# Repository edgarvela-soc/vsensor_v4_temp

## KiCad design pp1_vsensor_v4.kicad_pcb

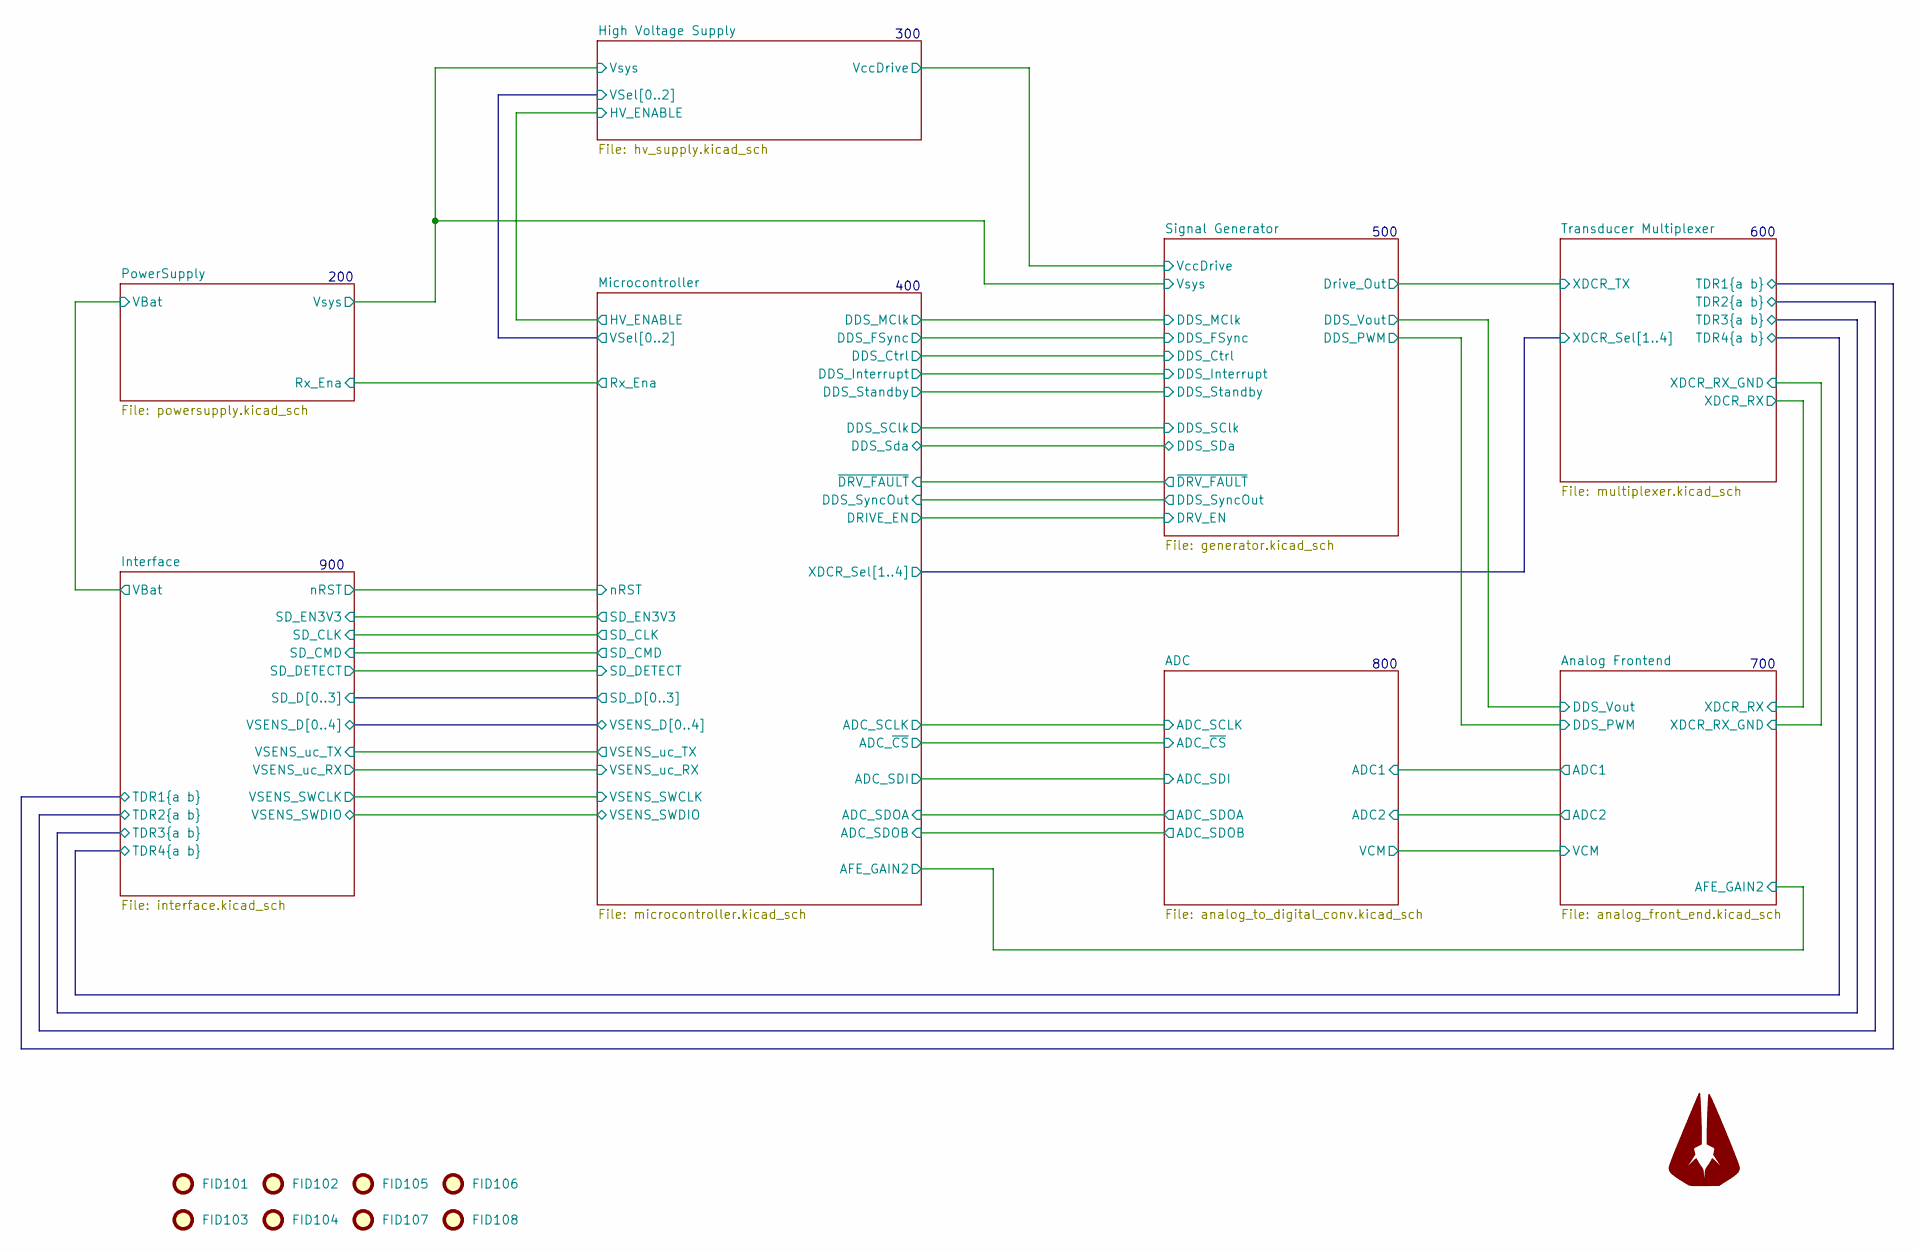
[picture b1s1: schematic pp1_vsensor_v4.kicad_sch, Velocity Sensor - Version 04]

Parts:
FID101, FID102, FID103, FID104, FID105, FID106, FID107, FID108: Fiducial; Fiducial_0.5mm_Mask1mm
Logo101: LOGO_AGU; AGU_15mm

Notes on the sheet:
700
400
800
500
300
600
900
200

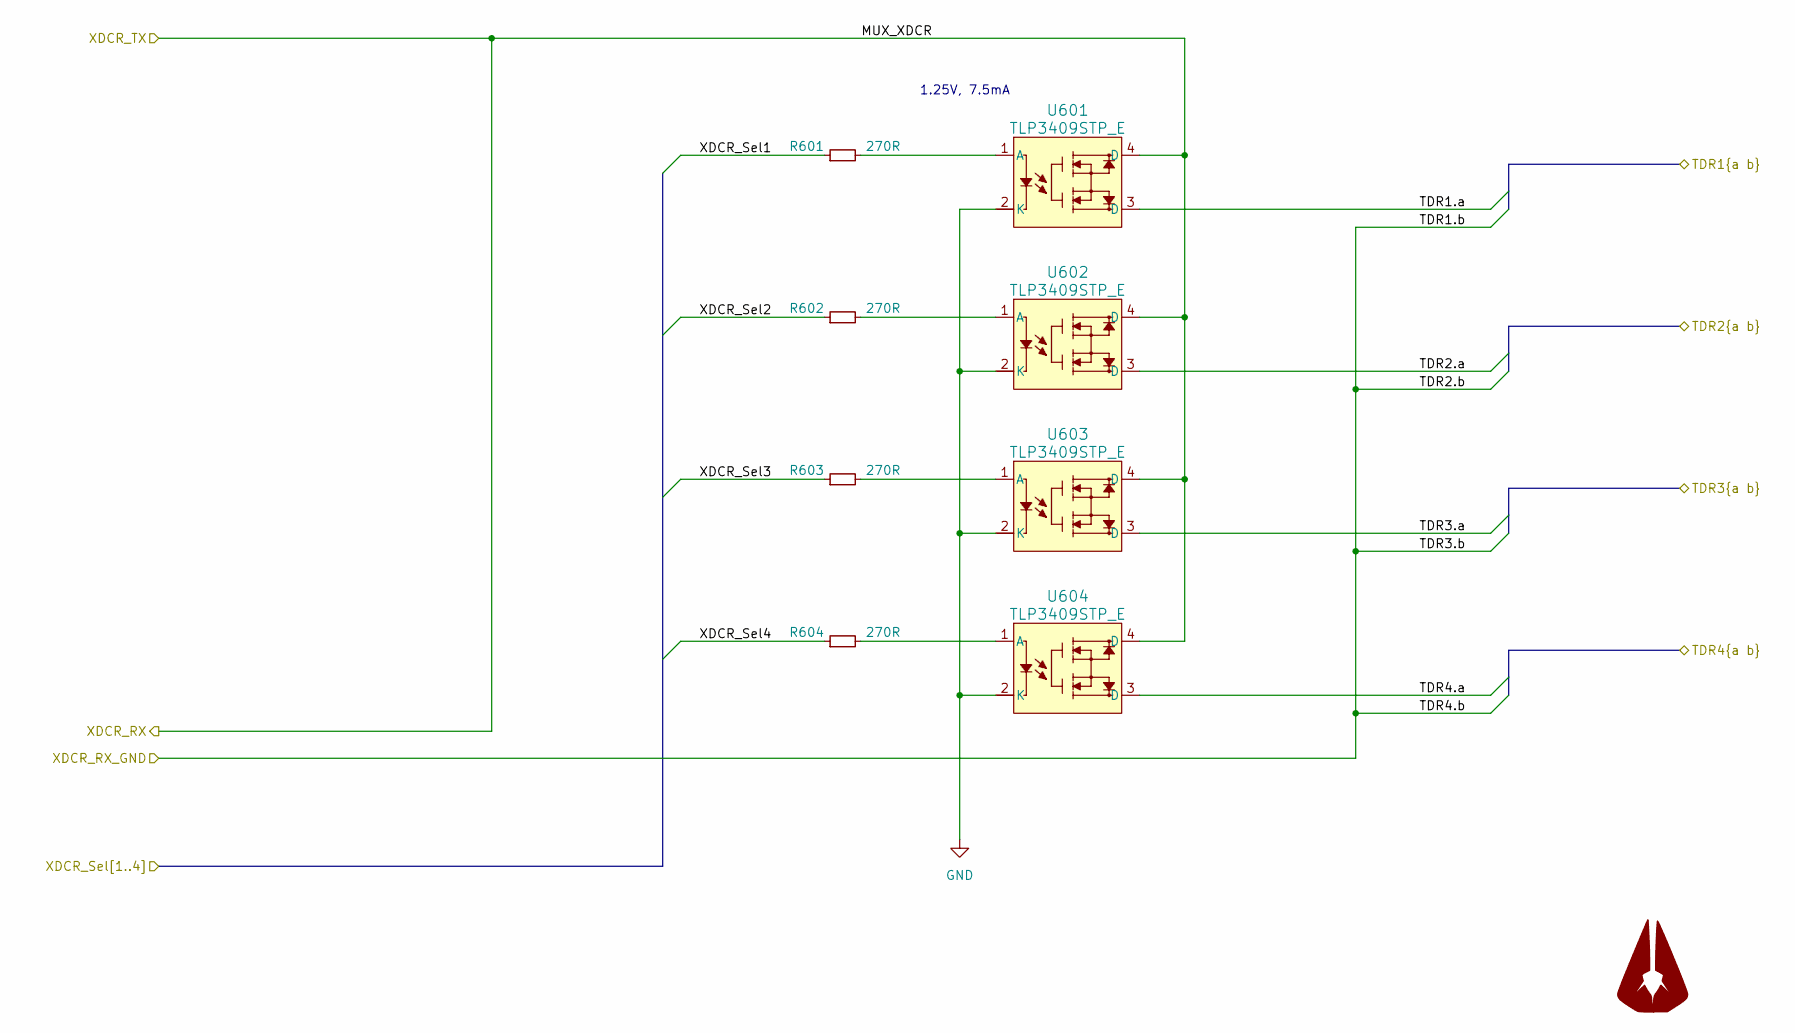
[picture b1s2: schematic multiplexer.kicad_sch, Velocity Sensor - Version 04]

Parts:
Logo601: LOGO_AGU; AGU_15mm
R601, R602, R603, R604: 270R; R_0402_1005Metric; MPN RMCF0402FT270R; Digikey_PN RMCF0402FT270RCT-ND
U601, U602, U603, U604: TLP3409STP_E; MPN TLP3409S(TP,E; Mouser_PN 757-TLP3409STPE

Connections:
/Interface/TDR1.a: U601.3 (D); also elsewhere on the board
/Interface/TDR2.a: U602.3 (D); also elsewhere on the board
/Interface/TDR3.a: U603.3 (D); also elsewhere on the board
/Interface/TDR4.a: U604.3 (D); also elsewhere on the board
/Microcontroller/XDCR_Sel1: R601.1; also elsewhere on the board
/Microcontroller/XDCR_Sel2: R602.1; also elsewhere on the board
/Microcontroller/XDCR_Sel3: R603.1; also elsewhere on the board
/Microcontroller/XDCR_Sel4: R604.1; also elsewhere on the board
/Transducer Multiplexer/MUX_XDCR: U601.4 (D), U602.4 (D), U603.4 (D), U604.4 (D); also elsewhere on the board
unnamed: R601.2, U601.1 (A)
unnamed: R602.2, U602.1 (A)
unnamed: R603.2, U603.1 (A)
unnamed: R604.2, U604.1 (A)

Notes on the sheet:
1.25V, 7.5mA

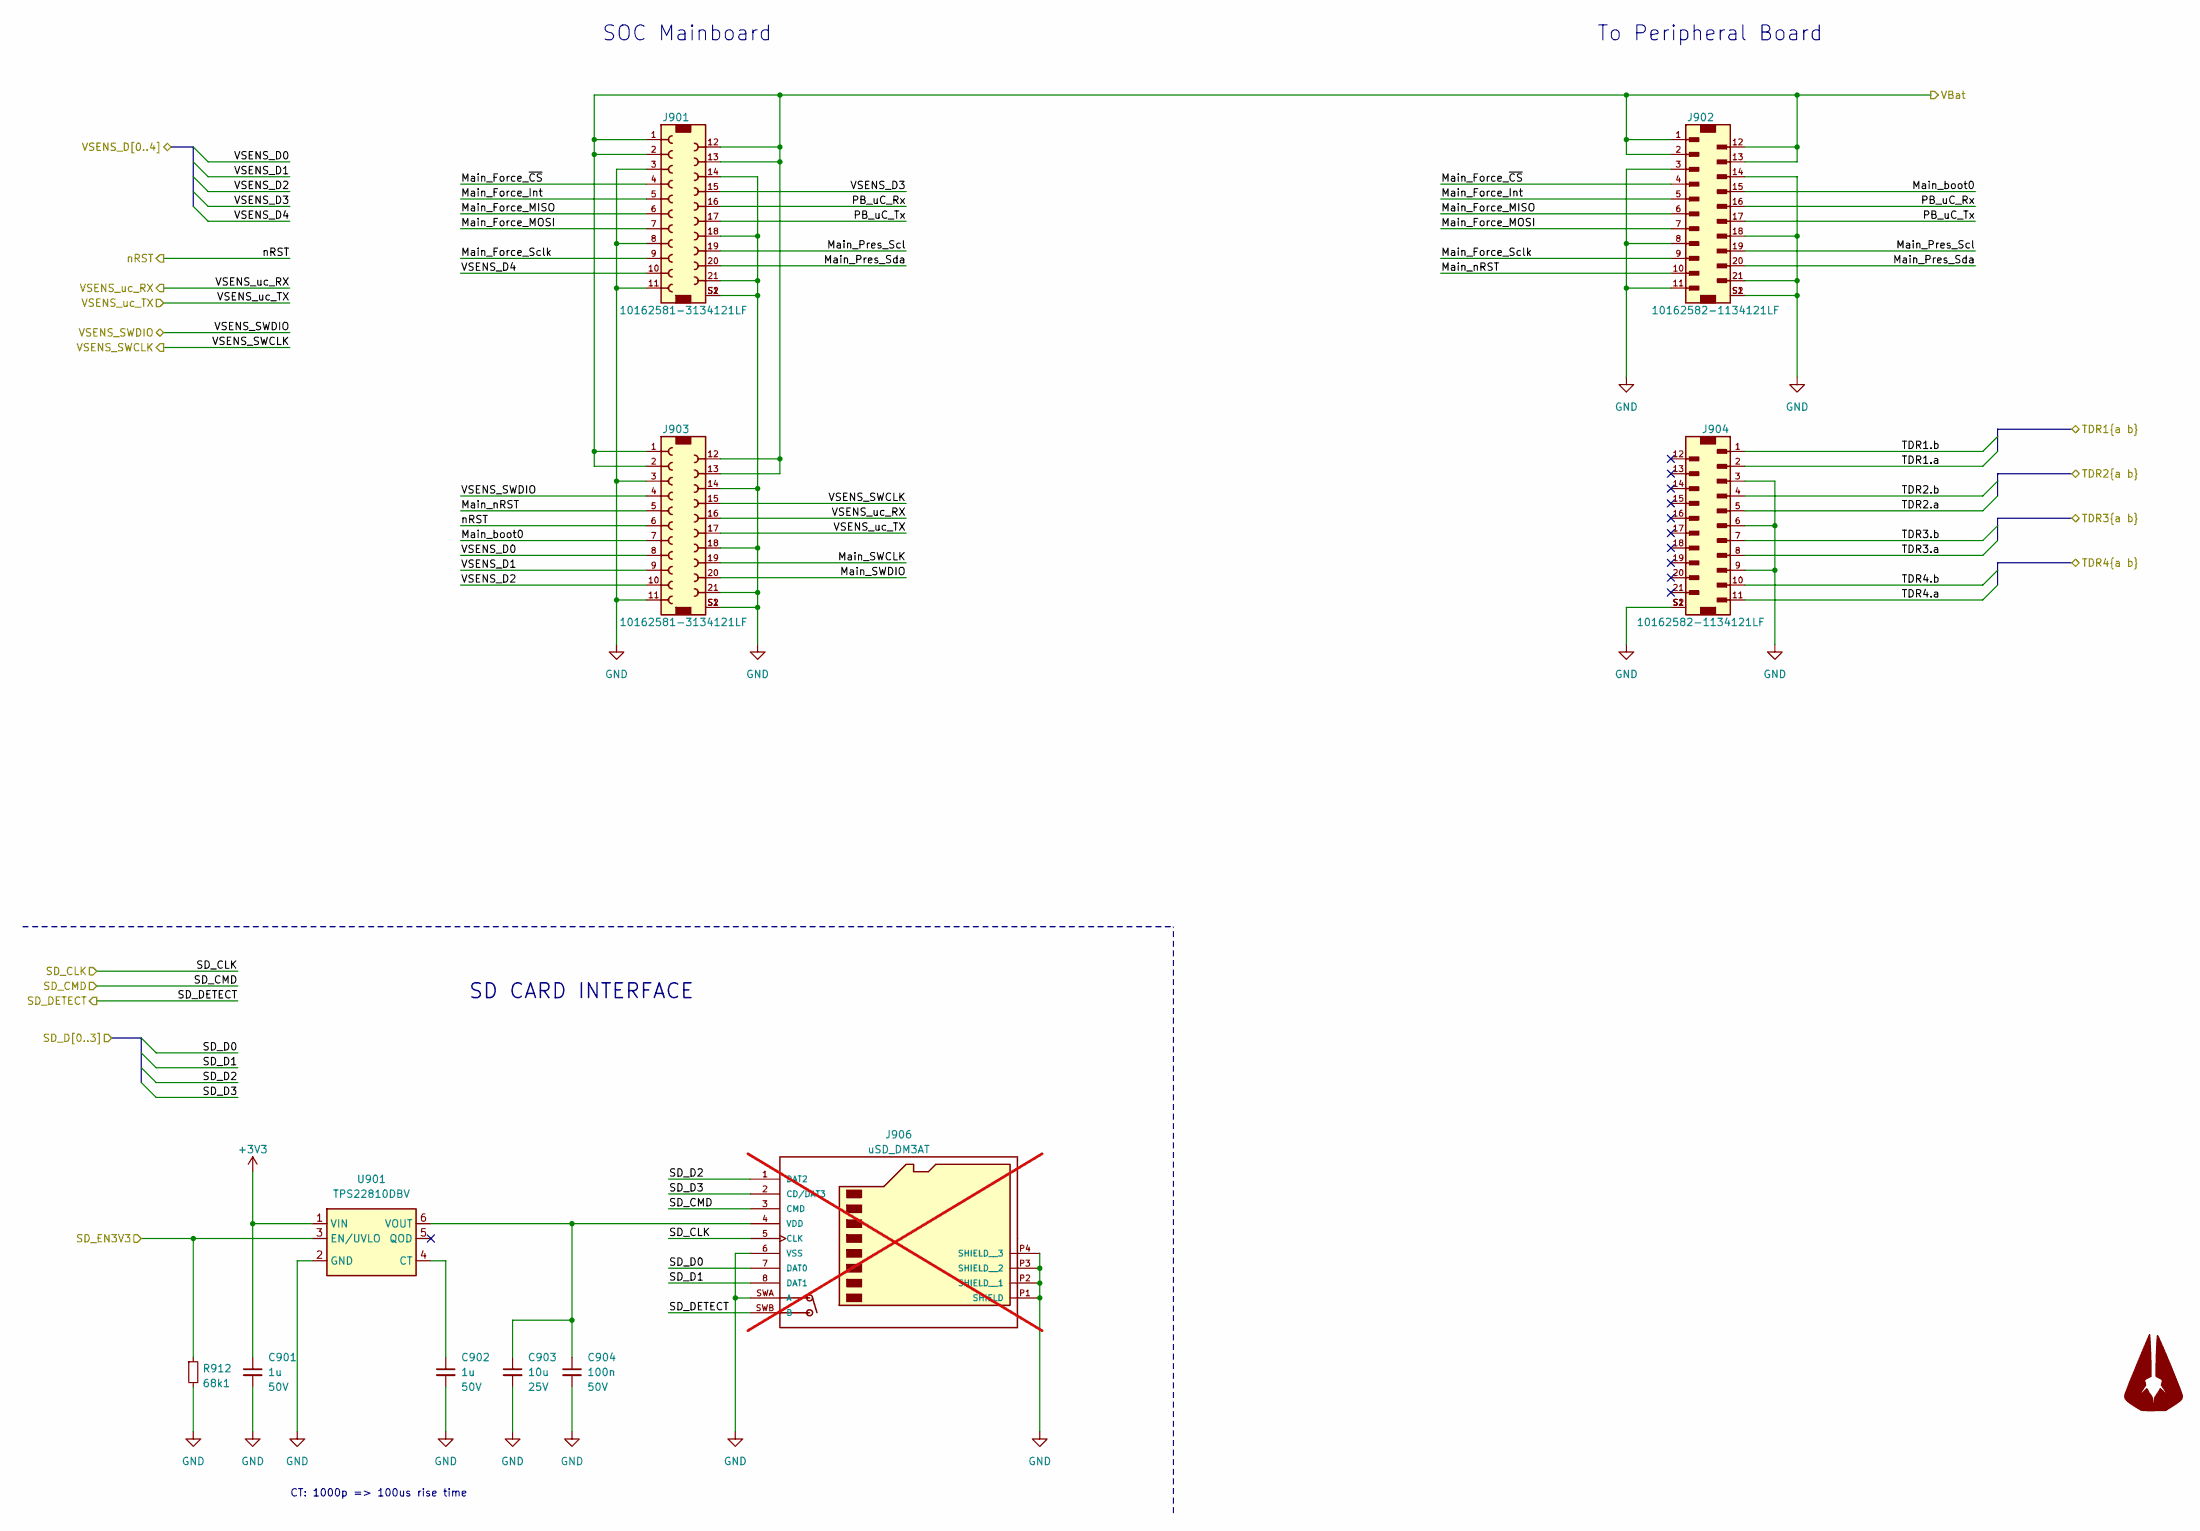
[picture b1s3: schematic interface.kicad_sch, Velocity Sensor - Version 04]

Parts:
C901, C902: 1u; C_0402_1005Metric; Voltage 50V; MPN UMK105CBJ105MV-F; Digikey_PN 587-6278-1-ND
C903: 10u; C_0603_1608Metric; Voltage 25V; MPN GRM188R61E106MA73D; Mouser_PN 81-GRM188R61E106MA3D
C904: 100n; C_0402_1005Metric; Voltage 50V; MPN CC0402KRX7R9BB104; Digikey_PN 311-3566-1-ND
J901, J903: 10162581-3134121LF; AMPHENOL_10162581-3134121LF; MPN 10162581-3134121LF; Digikey_PN 609-10162581-3134121LFCT-ND
J902, J904: 10162582-1134121LF; AMPHENOL_10162582-1134121LF; MPN 10162582-1134121LF; Digikey_PN 609-10162582-1134121LFCT-ND
J906: uSD_DM3AT; HRS_DM3AT-SF-PEJM5; PARTREV 20200913; Digikey_PN HR1964CT-ND; not fitted
Logo901: LOGO_AGU; AGU_15mm
R912: 68k1; R_0402_1005Metric; MPN RC0402FR-0768K1L; Digikey_PN YAG3213CT-ND
U901: TPS22810DBV; SOT95P280X145-6N; MPN TPS22810TDBVRQ1; Digikey_PN 296-50496-1-ND

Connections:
+3V3: C901.1, U901.1 (VIN); also elsewhere on the board
/Interface/Main_Force_Int: J901.5, J902.5
/Interface/Main_Force_MISO: J901.6, J902.6
/Interface/Main_Force_MOSI: J901.7, J902.7
/Interface/Main_Force_Sclk: J901.9, J902.9
/Interface/Main_Force_~CS: J901.4, J902.4
/Interface/Main_Pres_Scl: J901.19, J902.19
/Interface/Main_Pres_Sda: J901.20, J902.20
/Interface/Main_SWCLK: J903.19
/Interface/Main_SWDIO: J903.20
/Interface/Main_boot0: J902.15, J903.7
/Interface/Main_nRST: J902.10, J903.5
/Interface/PB_uC_Rx: J901.16, J902.16
/Interface/PB_uC_Tx: J901.17, J902.17
/Interface/SD_CLK: J906.5 (CLK); also elsewhere on the board
/Interface/SD_CMD: J906.3 (CMD); also elsewhere on the board
/Interface/SD_D0: J906.7 (DAT0); also elsewhere on the board
/Interface/SD_D1: J906.8 (DAT1); also elsewhere on the board
/Interface/SD_D2: J906.1 (DAT2); also elsewhere on the board
/Interface/SD_D3: J906.2 (CD/DAT3); also elsewhere on the board
/Interface/SD_DETECT: J906.SWB (B); also elsewhere on the board
/Interface/TDR1.a: J904.2; also elsewhere on the board
/Interface/TDR2.a: J904.5; also elsewhere on the board
/Interface/TDR3.a: J904.8; also elsewhere on the board
/Interface/TDR4.a: J904.11; also elsewhere on the board
/Interface/VBat: J901.1, J901.2, J901.12, J901.13, J902.1, J902.2, J902.12, J902.13, J903.1, J903.2, J903.12, J903.13; also elsewhere on the board
/Interface/VSENS_D0: J903.8; also elsewhere on the board
/Interface/VSENS_D1: J903.9; also elsewhere on the board
/Interface/VSENS_D2: J903.10; also elsewhere on the board
/Interface/VSENS_D3: J901.15; also elsewhere on the board
/Interface/VSENS_D4: J901.10; also elsewhere on the board
/Interface/VSENS_SWCLK: J903.15; also elsewhere on the board
/Interface/VSENS_SWDIO: J903.4; also elsewhere on the board
/Interface/VSENS_uc_RX: J903.16; also elsewhere on the board
/Interface/VSENS_uc_TX: J903.17; also elsewhere on the board
/Interface/nRST: J903.6; also elsewhere on the board
/Microcontroller/SD_EN3V3: R912.1, U901.3 (EN/UVLO); also elsewhere on the board
unnamed: C903.1, C904.1, J906.4 (VDD), U901.6 (VOUT)
unnamed: C902.1, U901.4 (CT)

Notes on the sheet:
To Peripheral Board
SOC Mainboard
CT: 1000p => 100us rise time
SD CARD INTERFACE

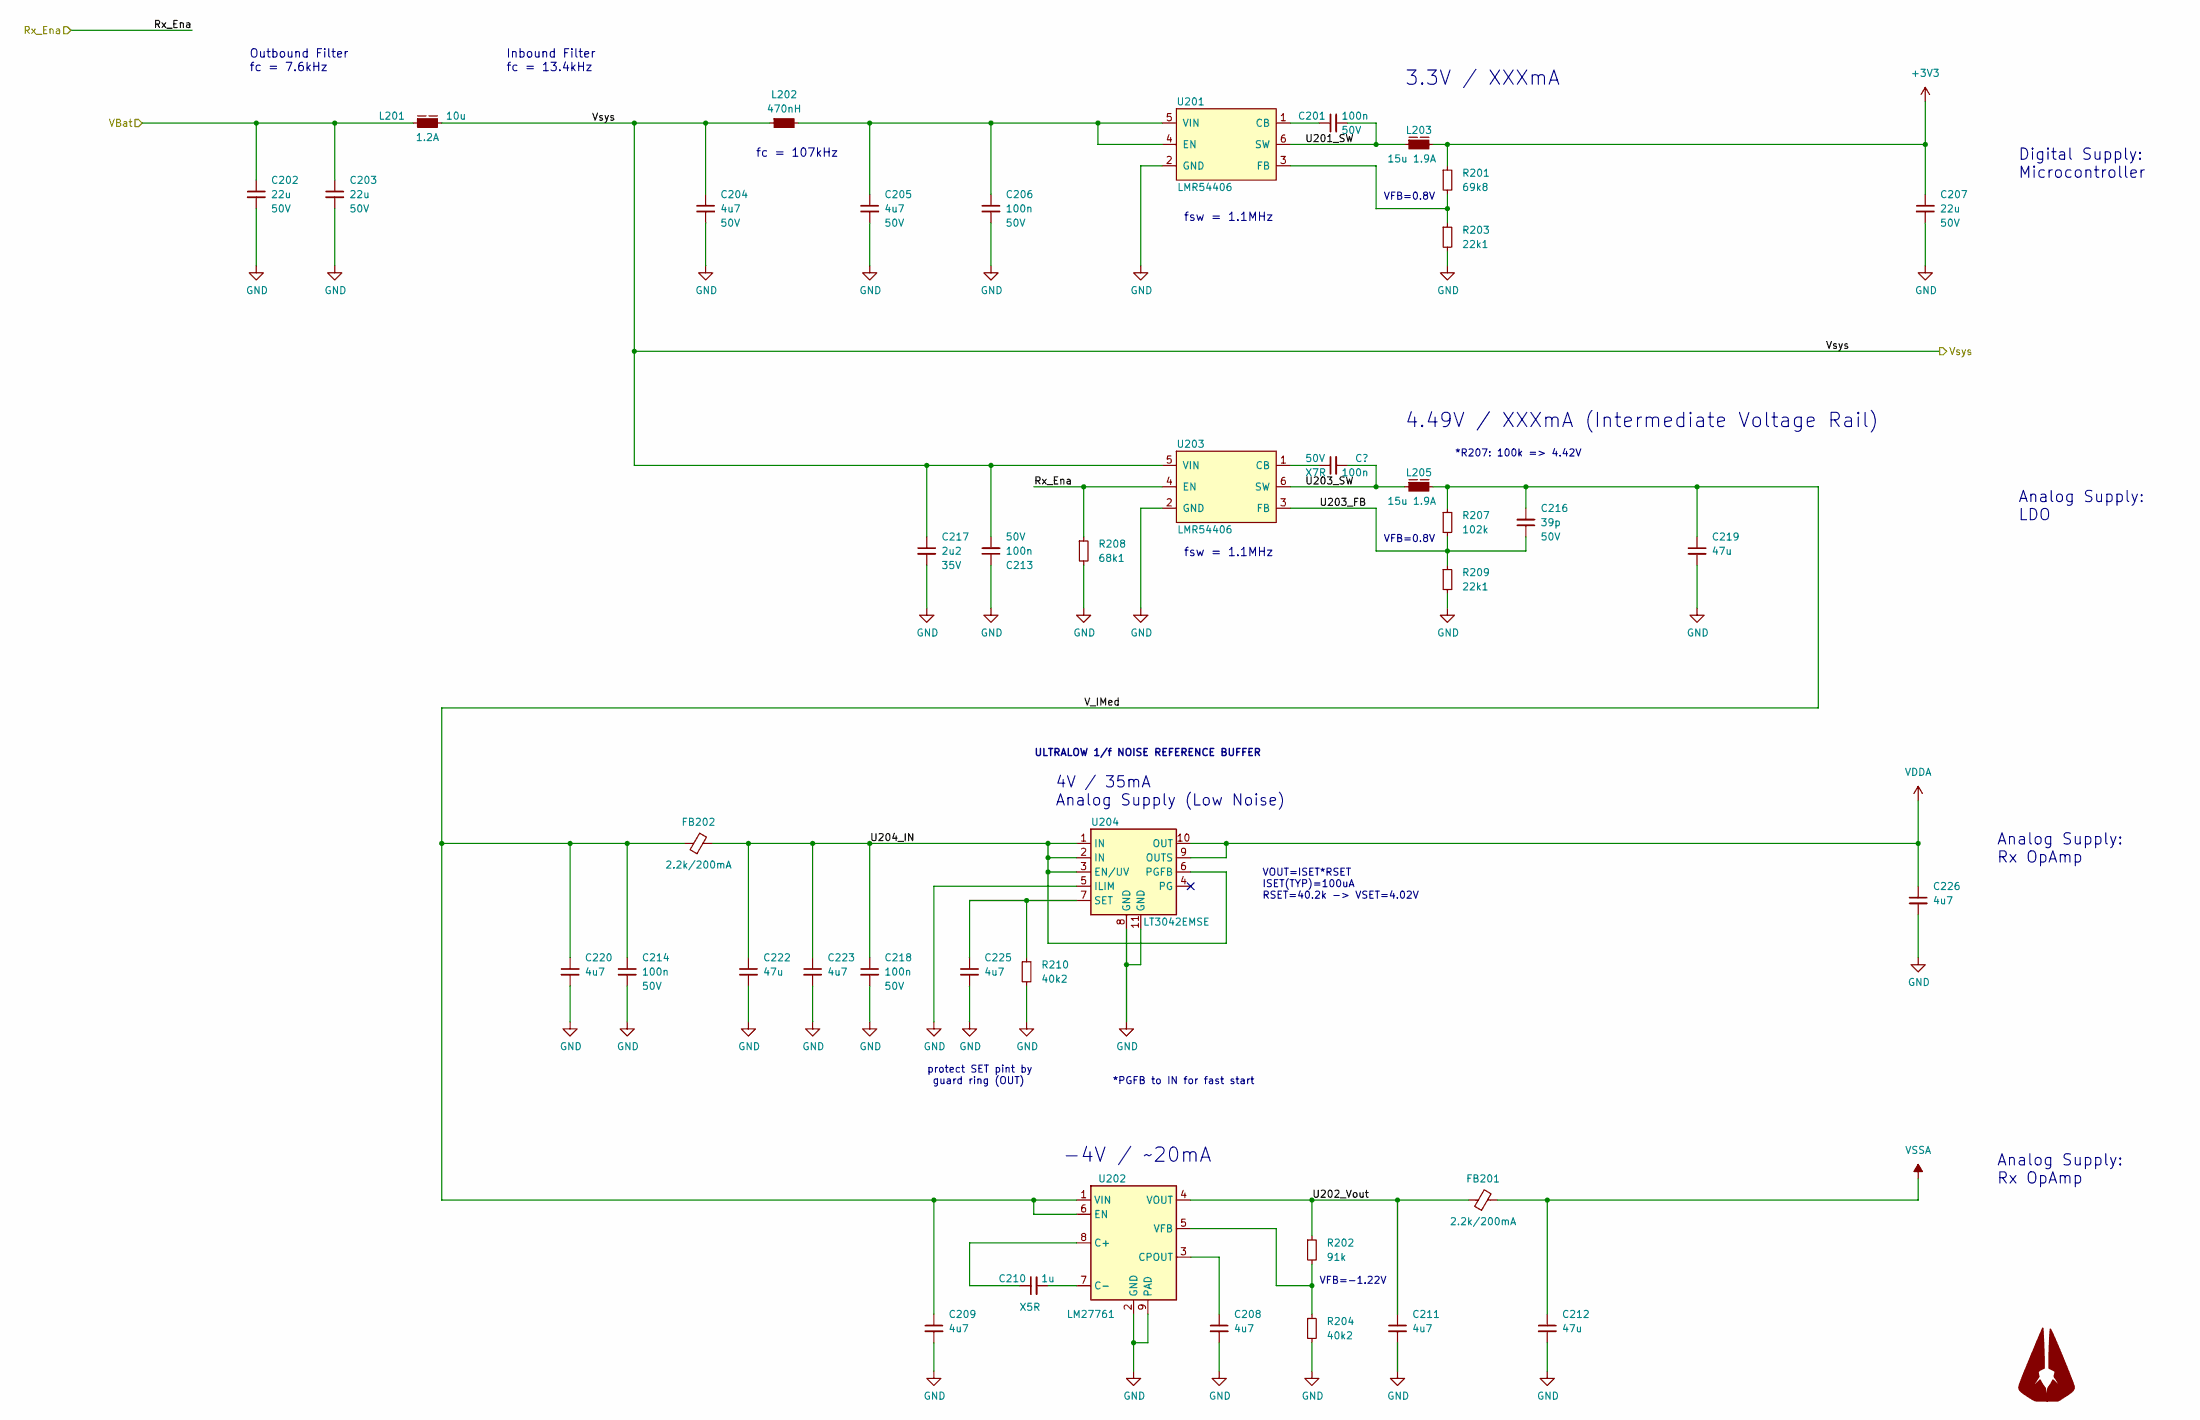
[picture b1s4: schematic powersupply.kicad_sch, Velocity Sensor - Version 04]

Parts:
C201, C206, C213, C214, C218: 100n; C_0402_1005Metric; Voltage 50V; MPN CC0402KRX7R9BB104; Digikey_PN 311-3566-1-ND
C202, C203, C207: 22u; C_2220_5650Metric; Voltage 50V; MPN C5750X7R1H226M250KB; Digikey_PN 445-C5750X7R1H226M250KBCT-ND
C204, C205: 4u7; C_1206_3216Metric; Voltage 50V; MPN GRM31CR71H475KA12K; Digikey_PN 490-GRM31CR71H475KA12KCT-ND
C208, C209, C211, C220, C223, C225, C226: 4u7; C_0805_2012Metric; Voltage 50V; MPN CGA4J3X5R1H475K125AB; Mouser_PN 810-CGA4J3X5R1H475K
C210: 1u; C_0402_1005Metric; Voltage 50V; MPN UMK105CBJ105MV-F; Digikey_PN 587-6278-1-ND
C212, C219, C222: 47u; C_1206_3216Metric; Voltage 16V; MPN C3216X5R1C476M160AB; Digikey_PN 445-6003-1-ND
C216: 39p; C_0402_1005Metric; VOLTAGE 50V; Voltage 50V; MPN CC0402FRNPO9BN390; Digikey_PN 311-3733-1-ND
C217: 2u2; C_0805_2012Metric; Voltage 35V; MPN CGA4J1X7R1V225K125AC; Digikey_PN 445-6963-1-ND
FB201, FB202: 2.2k/200mA; L_0805_2012Metric; MPN 742792093; Digikey_PN 732-1609-1-ND
L201: 10u; L_Wuerth_MAPI-3020; MPN 74438336100; Digikey_PN 732-5700-1-ND
L202: 470nH; L_0603_1608Metric; MPN LQM18PNR47NC0L; Digikey_PN 490-LQM18PNR47NC0LCT-ND
L203, L205: 15u 1.9A; L_Wuerth_MAPI-4020; MPN 74438356150; Digikey_PN 732-11663-1-ND
Logo201: LOGO_AGU; AGU_15mm
R201: 69k8; R_0402_1005Metric; MPN RC0402FR-0769K8L; Digikey_PN YAG3216CT-ND
R202: 91k; R_0402_1005Metric; MPN RC0402FR-0791KL; Digikey_PN 311-91.0KLRCT-ND
R203, R209: 22k1; R_0402_1005Metric; MPN RC0402FR-0722K1L; Digikey_PN 311-22.1KLRCT-ND
R204, R210: 40k2; R_0402_1005Metric; MPN RC0402FR-0740K2L; Digikey_PN 311-40.2KLRCT-ND
R207: 102k; R_0402_1005Metric; MPN RC0402FR-07102KL; Digikey_PN YAG2944CT-ND
R208: 68k1; R_0402_1005Metric; MPN RC0402FR-0768K1L; Digikey_PN YAG3213CT-ND
U201, U203: LMR54406; SOT-23-6; MPN LMR54406FDBVR; Digikey_PN 296-LMR54406FDBVRCT-ND
U202: LM27761; WSON-8-1EP_2x2mm_P0.5mm_EP0.9x1.6mm; MPN LM27761DSGR; Digikey_PN 296-44379-1-ND
U204: LT3042EMSE; MSOP-10-1EP_3x3mm_P0.5mm_EP1.68x1.88mm; MPN LT3042EMSE#TRPBF; Digikey_PN LT3042EMSE#TRPBFCT-ND

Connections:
+3V3: C207.1, L203.2, R201.1; also elsewhere on the board
/Interface/VBat: C202.1, C203.1, L201.1; also elsewhere on the board
/Microcontroller/Rx_Ena: R208.1, U203.4 (EN); also elsewhere on the board
/PowerSupply/U201_SW: C201.2, L203.1, U201.6 (SW)
/PowerSupply/U202_Vout: C211.1, FB201.1, R202.1, U202.4 (VOUT)
unnamed: C201.1, U201.1 (CB)
unnamed: C205.1, C206.1, L202.2, U201.4 (EN), U201.5 (VIN)
unnamed: R201.2, R203.1, U201.3 (FB)
unnamed: C210.1, U202.8 (C+)
unnamed: C210.2, U202.7 (C-)
unnamed: C208.1, U202.3 (CPOUT)
unnamed: R202.2, R204.1, U202.5 (VFB)
unnamed: C225.1, R210.1, U204.7 (SET)
VDDA: C226.1, U204.9 (OUTS), U204.10 (OUT); also elsewhere on the board
VSSA: C212.1, FB201.2; also elsewhere on the board

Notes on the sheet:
Outbound Filter fc = 7.6kHz
Inbound Filter fc = 13.4kHz
*R207: 100k => 4.42V
fsw = 1.1MHz
fc = 107kHz
Analog Supply: Rx OpAmp
VFB=0.8V
Analog Supply: LDO
3.3V / XXXmA
4.49V / XXXmA (Intermediate Voltage Rail)
Digital Supply: Microcontroller
ULTRALOW 1/f NOISE REFERENCE BUFFER
VOUT=ISET*RSET ISET(TYP)=100uA RSET=40.2k -> VSET=4.02V
4V / 35mA Analog Supply (Low Noise)
protect SET pint by guard ring (OUT)
VFB=-1.22V
*PGFB to IN for fast start
-4V / ~20mA

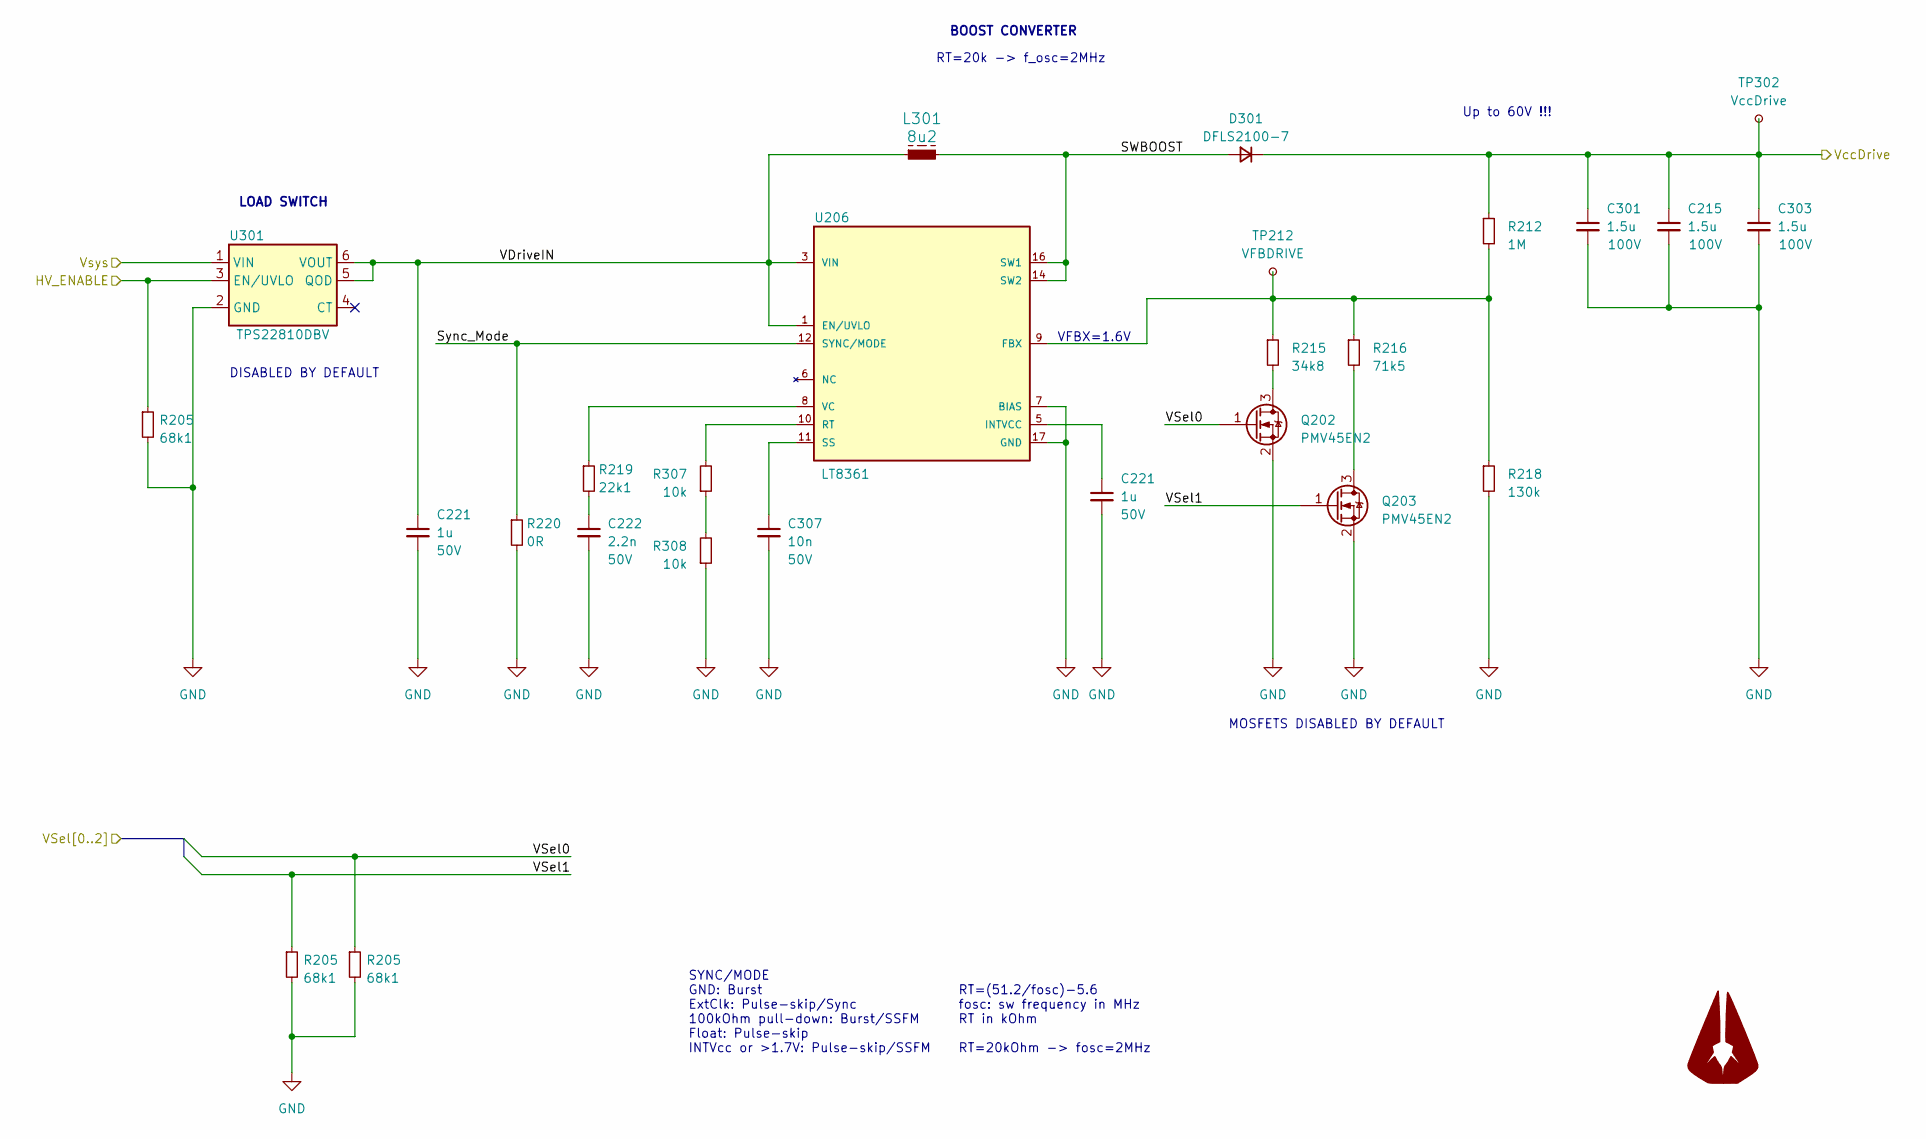
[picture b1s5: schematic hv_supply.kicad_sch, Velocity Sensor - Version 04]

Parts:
C215, C301, C303: 1.5u; C_1206_3216Metric; Voltage 100V; MPN C3216X7S2A155K160AB; Mouser_PN 810-C3216X7S2A155K1B
C221: 1u; C_0402_1005Metric; Voltage 50V; MPN UMK105CBJ105MV-F; Digikey_PN 587-6278-1-ND
C222: 2.2n; C_0402_1005Metric; Voltage 50V; MPN C0402C222J5RAC7867; Digikey_PN 399-C0402C222J5RAC7867CT-ND
C307: 10n; C_0402_1005Metric; Voltage 50V; MPN GCM155R71H103KA55D; Digikey_PN 399-C0402C222J5RAC7867CT-ND
D301: DFLS2100-7; D_PowerDI-123; MPN DFLS2100-7; Mouser_PN 621-DFLS2100-7
L301: 8u2; IND25X25CZ; MPN IHLP2525CZER8R2M01; Digikey_PN 541-1012-1-ND
Logo301: LOGO_AGU; AGU_15mm
Q202, Q203: PMV45EN2; SOT-23; MPN PMV45EN2R; Mouser_PN 771-PMV45EN2R
R205: 68k1; R_0402_1005Metric; MPN RC0402FR-0768K1L; Digikey_PN YAG3213CT-ND
R212: 1M; R_0402_1005Metric; MPN CRGCQ0402F1M0; Digikey_PN A129663CT-ND
R215: 34k8; R_0402_1005Metric; MPN RMCF0402FT34K8; Digikey_PN RMCF0402FT34K8CT-ND
R216: 71k5; R_0402_1005Metric; MPN RC0402FR-0771K5L; Digikey_PN YAG3222CT-ND
R218: 130k; R_0402_1005Metric; MPN RC0402FR-07130KL; Digikey_PN YAG2969CT-ND
R219: 22k1; R_0402_1005Metric; MPN RC0402FR-0722K1L; Digikey_PN 311-22.1KLRCT-ND
R220: 0R; R_0402_1005Metric; MPN RC0402JR-070RL; Digikey_PN 311-0.0JRCT-ND
R307, R308: 10k; R_0402_1005Metric; MPN RC1005F103CS; Digikey_PN 1276-3431-1-ND
TP212: VFBDRIVE; TestPoint_Pad_D1.0mm
TP302: VccDrive; TestPoint_Pad_D1.0mm
U206: LT8361; SOP50P490X110-17N; MPN LT8361HMSE#PBF; Digikey_PN 505-LT8361HMSE#PBF-ND
U301: TPS22810DBV; SOT95P280X145-6N; MPN TPS22810TDBVRQ1; Digikey_PN 296-50496-1-ND

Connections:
/High Voltage Supply/SWBOOST: D301.2 (A), L301.2; also elsewhere on the board
/High Voltage Supply/VDriveIN: L301.1, U301.5 (QOD), U301.6 (VOUT); also elsewhere on the board
/Microcontroller/HV_ENABLE: U301.3 (EN/UVLO); also elsewhere on the board
unnamed: R307.1, R308.2
unnamed 132: R307.2; also elsewhere on the board
unnamed 133: C307.1; also elsewhere on the board

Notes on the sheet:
RT=(51.2/fosc)-5.6 fosc: sw frequency in MHz RT in kOhm RT=20kOhm -> fosc=2MHz
LOAD SWITCH
DISABLED BY DEFAULT
Up to 60V !!!
SYNC/MODE GND: Burst ExtClk: Pulse-skip/Sync 100kOhm pull-down: Burst/SSFM Float: Pulse-skip INTVcc or >1.7V: Pulse-skip/SSFM
MOSFETS DISABLED BY DEFAULT
RT=20k -> f_osc=2MHz
BOOST CONVERTER
VFBX=1.6V

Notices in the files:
parts and their libraries:
Copyright 2021 Accelerated Designs. All rights reserved.
